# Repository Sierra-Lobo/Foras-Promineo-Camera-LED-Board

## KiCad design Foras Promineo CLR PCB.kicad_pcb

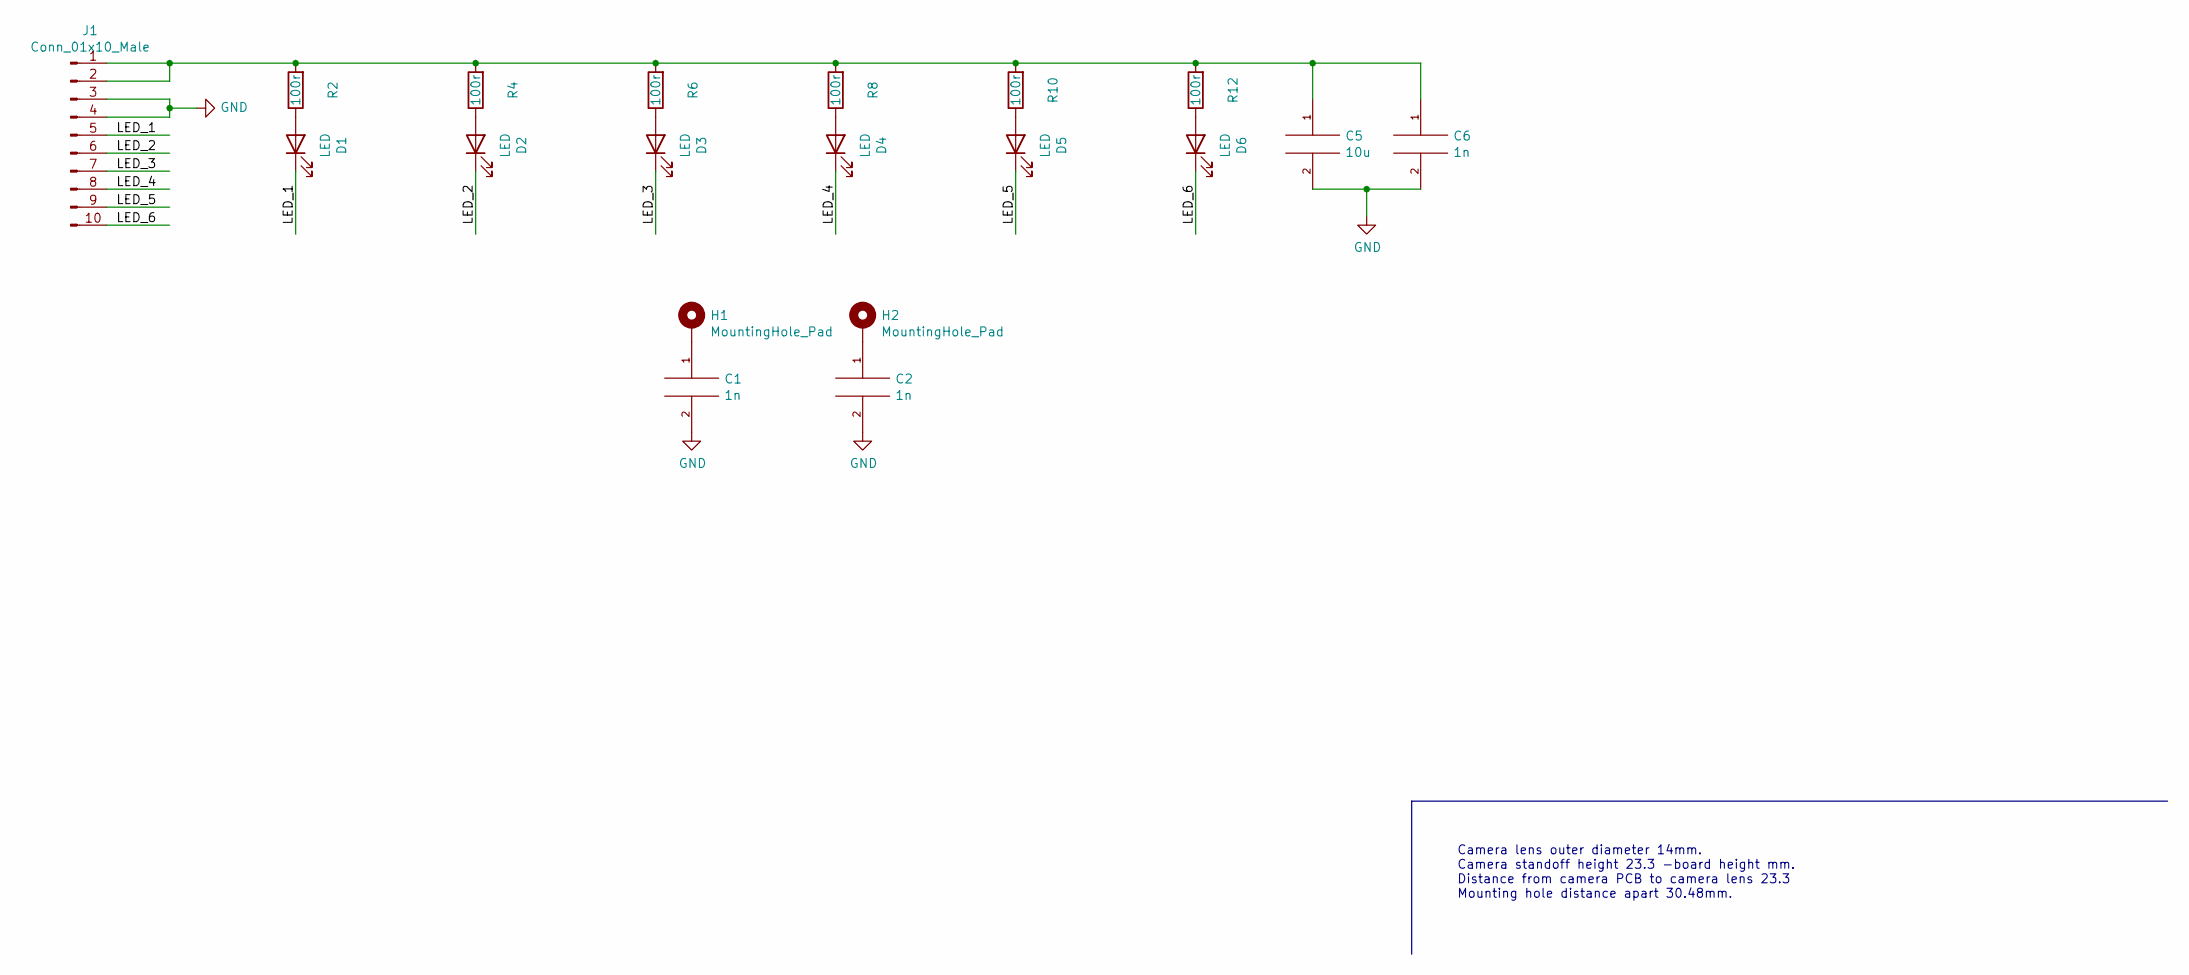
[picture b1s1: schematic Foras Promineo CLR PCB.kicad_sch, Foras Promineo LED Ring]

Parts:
C1, C2, C6: 1n; C_0603_1608Metric_Pad1.08x0.95mm_HandSolder; Manufacturer Part Number 0603ZC102KAT2A
C5: 10u; C_0603_1608Metric_Pad1.08x0.95mm_HandSolder; Manufacturer Part Number EMK107BBJ106MA-T
D1, D2, D3, D4, D5, D6: LED; 1212_LED_Pol; Manufacturer Part Number SPMWHD32AMH1XAH0S0
H1, H2: MountingHole_Pad; MountingHole_2.7mm_M2.5_DIN965_Pad
J1: Conn_01x10_Male; SAMTEC_T1M-05-X-DV; Manufacturer Part Number T1M-05-GF-DV-K
R2, R4, R6, R8, R10, R12: 100r; C_0603_1608Metric_Pad1.08x0.95mm_HandSolder; Manufacturer Part Number SDR03EZPJ101

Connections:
/LED_1: D1.1 (K), J1.5
/LED_2: D2.1 (K), J1.6
/LED_3: D3.1 (K), J1.7
/LED_4: D4.1 (K), J1.8
/LED_5: D5.1 (K), J1.9
/LED_6: D6.1 (K), J1.10
GND: C1.2, C2.2, C5.2, C6.2, J1.3, J1.4
unnamed: C1.1, H1.1
unnamed: C2.1, H2.1
unnamed: D1.2 (A), R2.1
unnamed: D2.2 (A), R4.1
unnamed: D3.2 (A), R6.1
unnamed: D4.2 (A), R8.1
unnamed: D5.2 (A), R10.1
unnamed: D6.2 (A), R12.1
unnamed: C5.1, C6.1, J1.1, J1.2, R2.2, R4.2, R6.2, R8.2, R10.2, R12.2

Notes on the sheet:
Camera lens outer diameter 14mm. Camera standoff height 23.3 -board height mm. Distance from camera PCB to camera lens 23.3 Mounting hole distance apart 30.48mm.

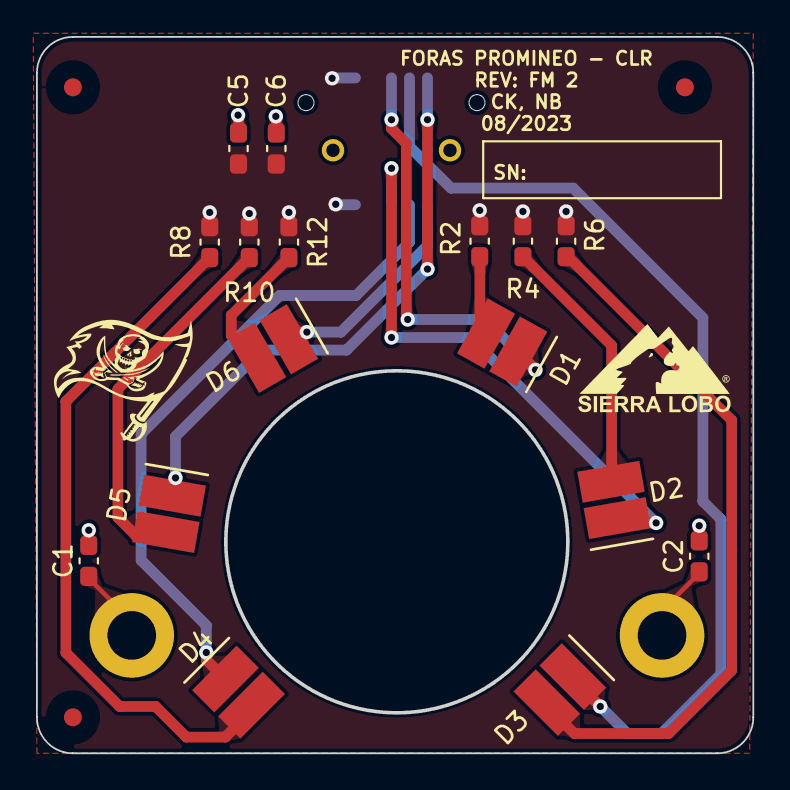
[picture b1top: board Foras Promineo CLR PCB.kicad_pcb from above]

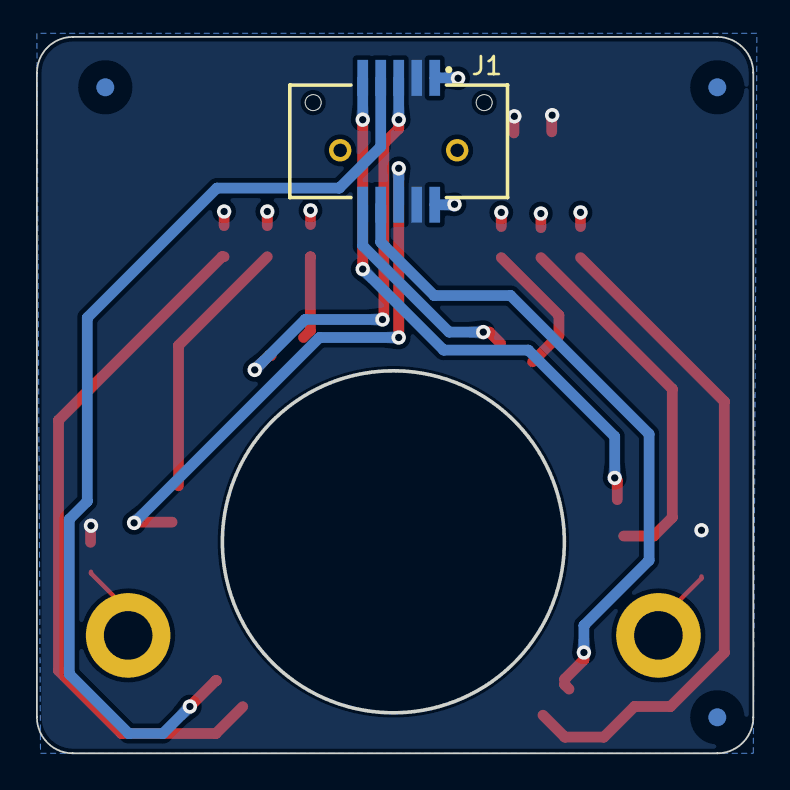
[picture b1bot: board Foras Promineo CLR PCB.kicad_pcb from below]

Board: 2 copper layers, 39.7 x 39.7 mm, 20 parts (2 on the bottom side), 16 nets.

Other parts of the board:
REFe: Fiducial_1mm_Mask3mm

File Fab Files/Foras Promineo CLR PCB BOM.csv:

"Source:","C:\Users\ckkornowski\Documents\GitHub\Foras-Promineo-Camera-LED-Board\Foras Promineo CLR PCB.kicad_sch"
"Date:","6/18/2022 9:43:49 PM"
"Tool:","Eeschema (6.0.2)"
"Generator:","C:\Users\ckkornowski\Documents\GitHub\Foras-Promineo-KiCad-Lib/bom_csv_grouped_by_value_with_fp_CK_USE_THIS.py"
"Component Count:","19"
"Ref","Qnty","Value","Cmp name","Footprint","Description","Vendor","Vendor Part Number","Manufacturer","Manufacturer Part Number"
"C1, C2, C6, ","3","1n","CAP","Capacitor_SMD:C_0603_1608Metric_Pad1.08x0.95mm_HandSolder","Capacitor symbol for simulation only","","","KYOCERA AVX","0603ZC102KAT2A"
"C5, ","1","10u","CAP","Capacitor_SMD:C_0603_1608Metric_Pad1.08x0.95mm_HandSolder","Capacitor symbol for simulation only","","","Taiyo Yuden","EMK107BBJ106MA-T"
"D1, D2, D4, D5, D6, ","5","LED","LED","Foras_Promineo:1212_LED_Pol","Light emitting diode","","","Samsung Semiconductor, Inc.","SPMWHD32AMH1XAH0S0"
"D3, ","1","LED","LED","Foras_Promineo_Github_Local:1212_LED_Pol","Light emitting diode","","","Samsung Semiconductor, Inc.","SPMWHD32AMH1XAH0S0"
"H1, H2, ","2","MountingHole_Pad","MountingHole_Pad","MountingHole:MountingHole_3.5mm_Pad_Via","Mounting Hole with connection","","","",""
"J1, ","1","Conn_01x10_Male","Conn_01x10_Male","Foras_Promineo:SAMTEC_T1M-05-X-DV","Generic connector, single row, 01x10, script generated (kicad-library-utils/schlib/autogen/connector/)","","","Hirose Electric Co Ltd","DF13-10P-1.25DSA"
"R2, R4, R6, R8, R10, R12, ","6","100r","R","Capacitor_SMD:C_0603_1608Metric_Pad1.08x0.95mm_HandSolder","Resistor","","","Rohm Semiconductor","SDR03EZPJ101"

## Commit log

2022-04-14 Prototype
2022-06-19 FM DONE!
2022-09-07 FM Fab
2023-08-16 moved mounting holes and added fiducials
2023-08-16 saved
2023-08-18 LED RING
2023-08-25 Fixed LED board shape again...
2023-08-25 FM2 fab files
2023-10-02 assembly files
